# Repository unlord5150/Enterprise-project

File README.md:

Enterprise-project
==================

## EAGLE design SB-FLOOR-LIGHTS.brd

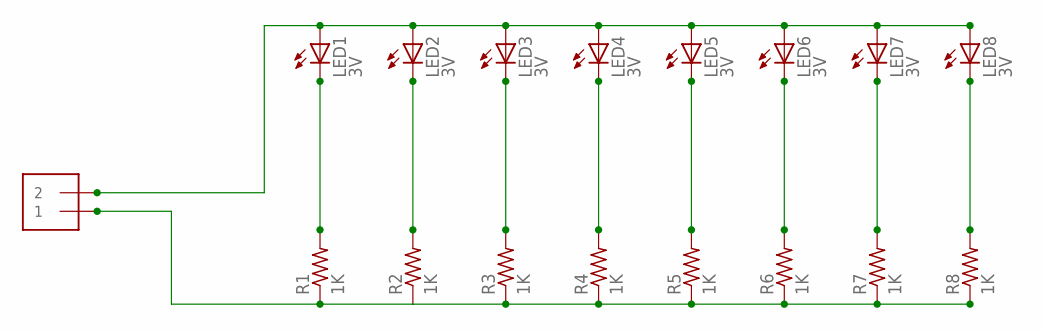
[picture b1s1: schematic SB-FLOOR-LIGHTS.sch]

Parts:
J1: 1X2-3.5MM
LED1, LED2, LED3, LED4, LED5, LED6, LED7, LED8: 3V; CHIPLED_0603
R1, R2, R3, R4, R5, R6, R7, R8: 1K; R0603

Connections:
unnamed: J1.1, R1.1, R2.1, R3.1, R4.1, R5.1, R6.1, R7.1, R8.1
unnamed: LED3.C, R3.2
unnamed: LED4.C, R4.2
unnamed: J1.2, LED1.A, LED2.A, LED3.A, LED4.A, LED5.A, LED6.A, LED7.A, LED8.A
unnamed: LED1.C, R1.2
unnamed: LED2.C, R2.2
unnamed: LED5.C, R5.2
unnamed: LED6.C, R6.2
unnamed: LED7.C, R7.2
unnamed: LED8.C, R8.2

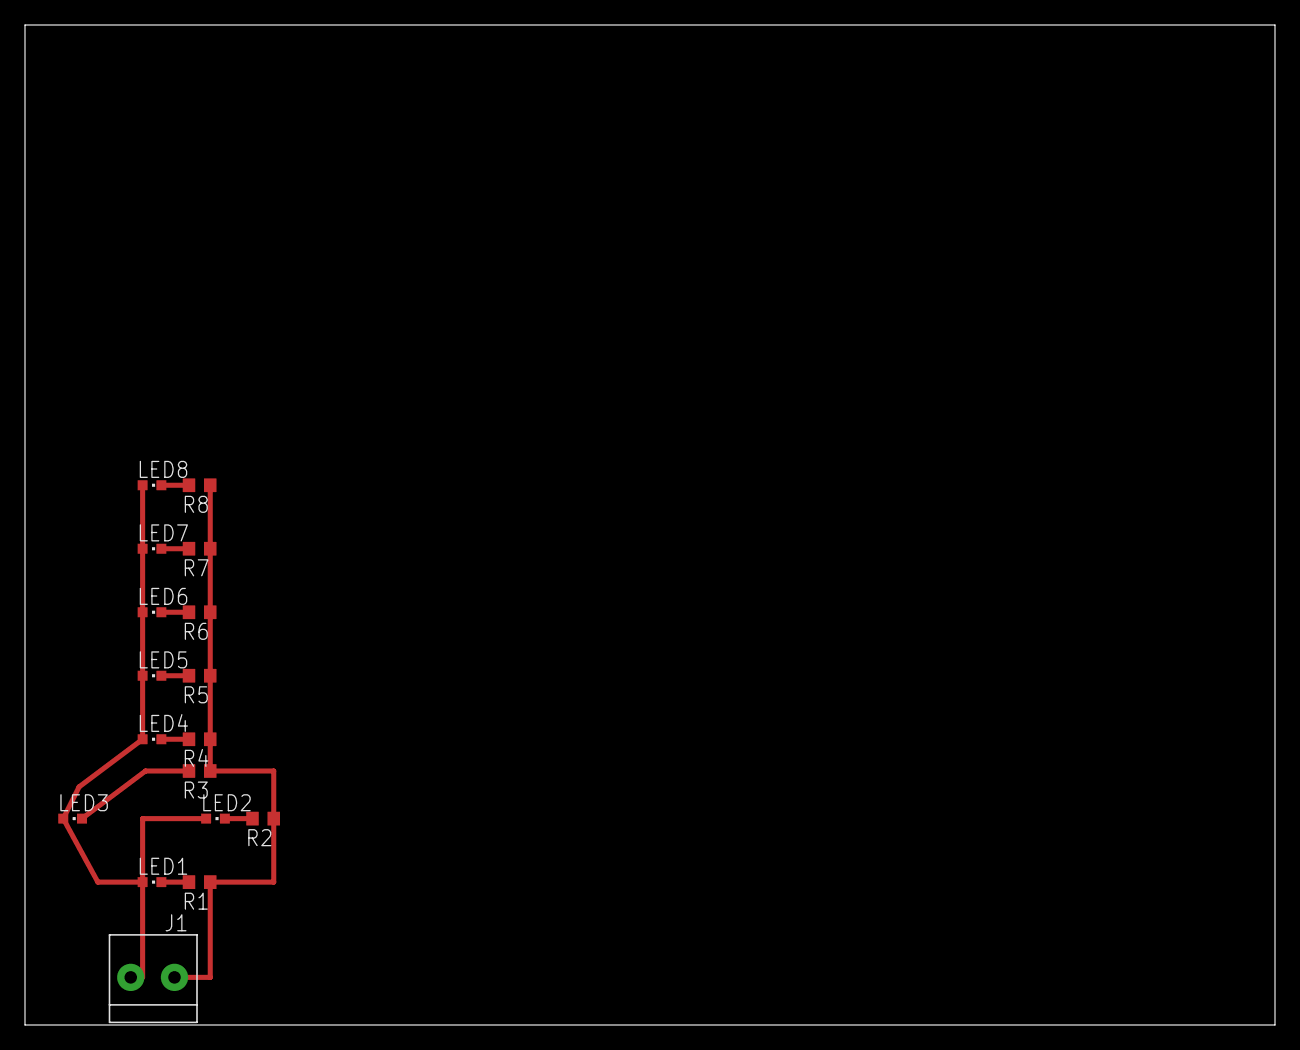
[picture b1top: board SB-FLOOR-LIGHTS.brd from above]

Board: 2 copper layers, 100.0 x 80.0 mm, 17 parts (0 on the bottom side), 10 nets.

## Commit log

2013-06-11 upload1
